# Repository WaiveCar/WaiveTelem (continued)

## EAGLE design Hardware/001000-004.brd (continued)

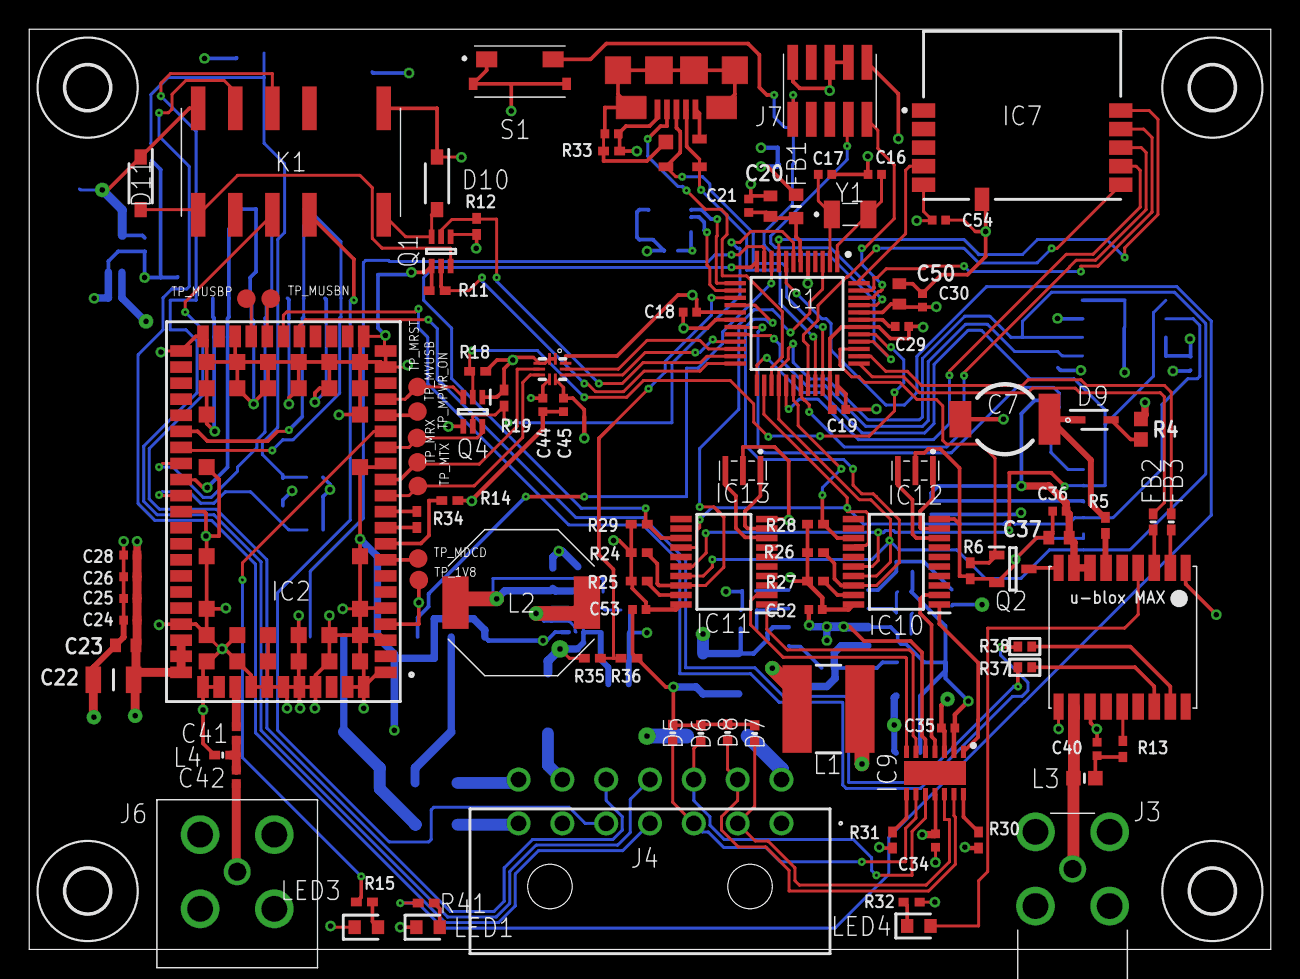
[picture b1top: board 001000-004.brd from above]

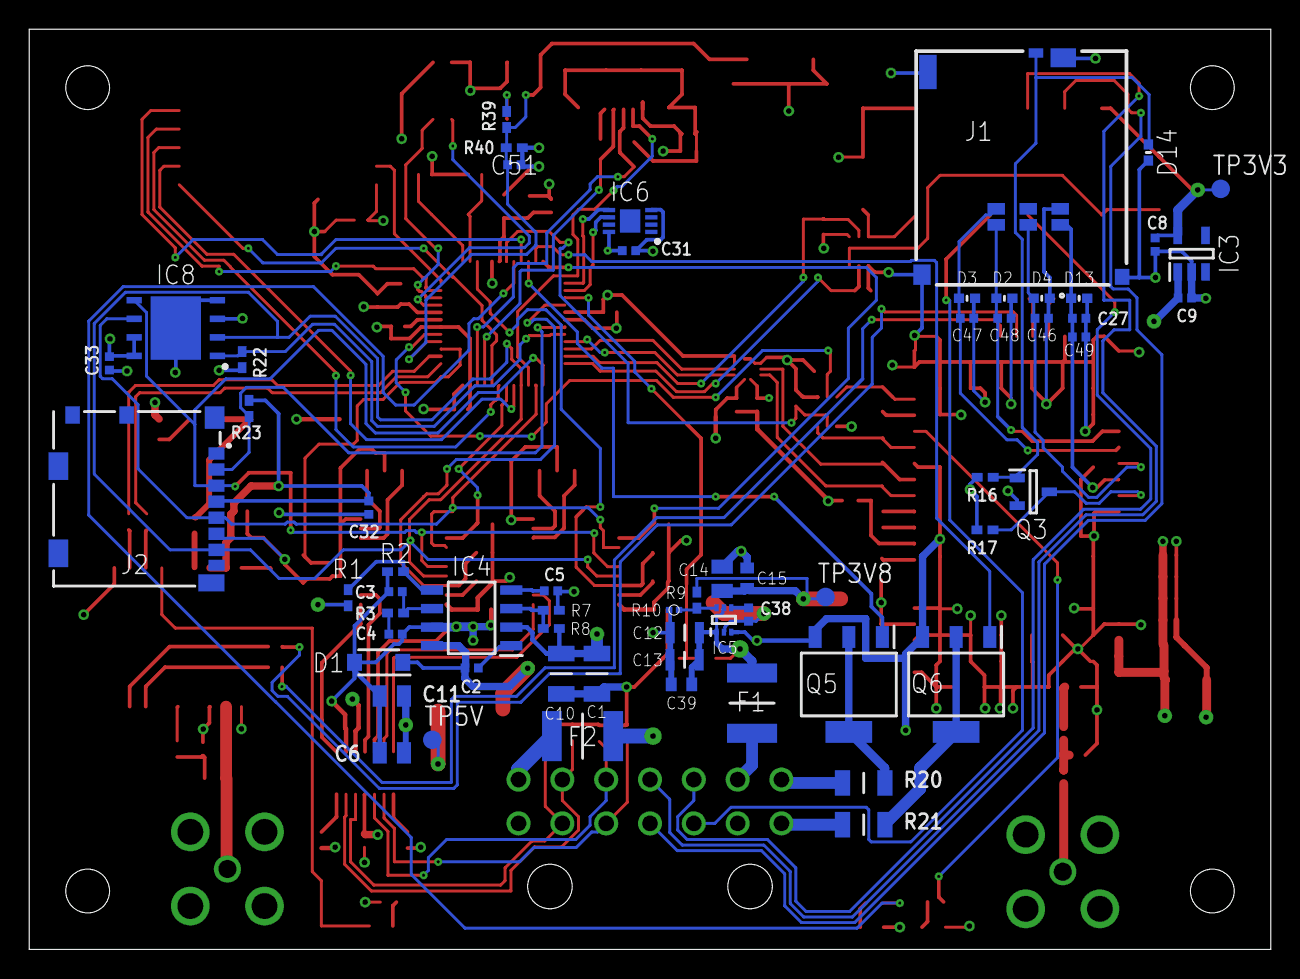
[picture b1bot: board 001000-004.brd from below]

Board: 4 copper layers, 85.0 x 63.0 mm, 168 parts (61 on the bottom side), 125 nets.

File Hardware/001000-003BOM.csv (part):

"Qty";"Value";"Device";"Package";"Parts";"Description";"CODE-ARDUINO";"DATASHEET";"DESCRIPTION";"DISTRIBUTOR-LINK";"DISTRIBUTOR-PN";"HEIGHT";"MANUFACTURER";"MANUFACTURER-PN";"MANUFACTURER_NAME";"MANUFACTURER_PART_NUMBER";"MOUSER_PART_NUMBER";"MOUSER_PRICE-STOCK";"NOTE";"RS_PART_NUMBER";"RS_PRICE-STOCK";"TP_SIGNAL_NAME";"VALUE";
"1";"-";"USB-MICRO";"ZX62-AB-5PA";"J5";"USB - micro AB USB 2.0 Receptacle Connector 5 Position Surface Mount, Right Angle, Horizontal";"2219";"https://www.hirose.com/product/en/download_file/key_name/ZX/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";"";"http://www.digikey.com/product-detail/en/hirose-electric-co-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";"H125279CT-ND ";"";"Hirose";"ZX62-AB-5PA(31) ";"";"";"";"";"";"";"";"";"-";
"3";"0R";"R_0402";"R0402";"R5, R14, R34";"RESISTOR";"";"";"";"";"";"";"";"";"";"";"";"";"";"";"";"";"";
"2";"0R";"R_1206";"R1206";"R20, R21";"RESISTOR";"";"";"";"";"";"";"";"";"";"";"";"";"";"";"";"";"";
"17";"100n";"C_0402";"C0402";"C2, C18, C19, C21, C24, C27, C30, C31, C33, C34, C35, C38, C44, C45, C52, C53, C54";"NON-POLARIZED CAP";"";"";"";"";"";"";"";"";"";"";"";"";"";"";"";"";"";
"1";"100p";"C-4N7-0402";"0402-1005X55N";"C51";"SMD Capacitor";"2266";"http://search.murata.co.jp/Ceramy/image/img/A01X/partnumberi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";"";"https://www.digikey.com/product-detail/en/murata-electronics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";"490-8259-1-ND";"";"Murata";"GRM155R71H472KA01J";"";"";"";"";"-";"";"";"";"4n7";
"1";"100u";"C_1206";"C1206";"C22";"NON-POLARIZED CAP";"";"";"";"";"";"";"";"";"";"";"";"";"";"";"";"";"";
"1";"1040310811";"1040310811";"1040310811";"J2";"MICRO SD card socket, push-pull 1.42H Normal type";"";"";"MICRO SD card socket, push-pull 1.42H Normal type";"";"";"mm";"";"";"Molex";"1040310811";"N/A";"https://www.mouser.com/Search/Refine.aspx?Keyword=N%2FA";"";"";"";"";"";
"1";"10R";"R_0402";"R0402";"R13";"RESISTOR";"";"";"";"";"";"";"";"";"";"";"";"";"";"";"";"";"";
"5";"10k";"R_0402";"R0402";"R15, R22, R23, R36, R40";"RESISTOR";"";"";"";"";"";"";"";"";"";"";"";"";"";"";"";"";"";
"1";"10k";"R_0603";"R0603";"R4";"RESISTOR";"";"";"";"";"";"";"";"";"";"";"";"";"";"";"";"";"";
"1";"10k2";"CRCW040210K2FKED";"RESC1005X40N";"R1";"CRCW0402 Resistor T/R 0.063W,1%,10K2 Vishay CRCW Series Thick Film Surface Mount Resistor 0402 Case 10.2k +/-1% 0.063W +/-100ppm/C";"";"";"CRCW0402 Resistor T/R 0.063W,1%,10K2 Vishay CRCW Series Thick Film Surface Mount Resistor 0402 Case 10.2k +/-1% 0.063W +/-100ppm/C";"";"";"0.4mm";"";"";"Vishay";"CRCW040210K2FKED";"71-CRCW0402-10.2K-E3";"https://www.mouser.com/Search/Refine.aspx?Keyword=71-CRCW040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";"";"";"";"";"";
"8";"10k2";"R_0402";"R0402";"R24, R25, R26, R27, R28, R29, R30, R31";"RESISTOR";"";"";"";"";"";"";"";"";"";"";"";"";"";"";"";"";"";
"1";"10n";"C_0402";"C0402";"C25";"NON-POLARIZED CAP";"";"";"";"";"";"";"";"";"";"";"";"";"";"";"";"";"";
"1";"10nF";"C_0402";"C0402";"C40";"NON-POLARIZED CAP";"";"";"";"";"";"";"";"";"";"";"";"";"";"";"";"";"";
"1";"10p";"C_0402";"C0402";"C3";"NON-POLARIZED CAP";"";"";"";"";"";"";"";"";"";"";"";"";"";"";"";"";"";
"1";"10u";"C_0402";"C0402";"C32";"NON-POLARIZED CAP";"";"";"";"";"";"";"";"";"";"";"";"";"";"";"";"";"";
"3";"10u";"C_0603";"C0603";"C20, C23, C50";"NON-POLARIZED CAP";"";"";"";"";"";"";"";"";"";"";"";"";"";"";"";"";"";
"2";"10u";"C_0805";"C0805";"C6, C11";"NON-POLARIZED CAP";"";"";"";"";"";"";"";"";"";"";"";"";"";"";"";"";"";
"1";"15p";"C_0402";"C0402";"C28";"NON-POLARIZED CAP";"";"";"";"";"";"";"";"";"";"";"";"";"";"";"";"";"";
"8";"1M2";"R_0402";"R0402";"R6, R11, R12, R16, R17, R18, R19, R33";"RESISTOR";"";"";"";"";"";"";"";"";"";"";"";"";"";"";"";"";"";
"1";"1k96";"CRCW04021K96FKED";"RESC1005X40N";"R2";"Vishay CRCW Series Thick Film Surface Mount Resistor 0402 Case 1.96k +/-1% 0.063W +/-100ppm/C";"";"";"Vishay CRCW Series Thick Film Surface Mount Resistor 0402 Case 1.96k +/-1% 0.063W +/-100ppm/C";"";"";"0.4mm";"";"";"Vishay";"CRCW04021K96FKED";"71-CRCW0402-1.96K-E3";"https://www.mouser.com/Search/Refine.aspx?Keyword=71-CRCW040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";"";"";"";"";"";
"3";"1u";"C_0402";"C0402";"C8, C9, C29";"NON-POLARIZED CAP";"";"";"";"";"";"";"";"";"";"";"";"";"";"";"";"";"";
"1";"1u";"C_0603";"C0603";"C37";"NON-POLARIZED CAP";"";"";"";"";"";"";"";"";"";"";"";"";"";"";"";"";"";
"2";"20p";"C_0402";"C0402";"C16, C17";"NON-POLARIZED CAP";"";"";"";"";"";"";"";"";"";"";"";"";"";"";"";"";"";
"1";"27nH";"L-14C27NJV4T";"INDC1608X95N";"L3";"Inductor RF Chip Multi-Layer 27nH 5% 100MHz 10Q-Factor Ceramic 300mA 600mOhm DCR 0603 T/R";"";"";"Inductor RF Chip Multi-Layer 27nH 5% 100MHz 10Q-Factor Ceramic 300mA 600mOhm DCR 0603 T/R";"";"";"0.95mm";"";"";"JOHANSON TECHNOLOGY";"L-14C27NJV4T";"";"";"";"";"";"";"";
"1";"28k";"R_0402";"R0402";"R3";"RESISTOR";"";"";"";"";"";"";"";"";"";"";"";"";"";"";"";"";"";
"2";"2N7002,215";"2N7002,215";"SOT95P230X110-3N";"Q2, Q3";"MOSFET N-Channel 60V 0.3A TO236AB NXP 2N7002,215 N-channel MOSFET Transistor, 0.3 A, 60 V, 3-Pin TO-236AB";"";"";"MOSFET N-Channel 60V 0.3A TO236AB NXP 2N7002,215 N-channel MOSFET Transistor, 0.3 A, 60 V, 3-Pin TO-236AB";"";"";"1.1mm";"";"";"Nexperia";"2N7002,215";"771-2N7002-T/R";"https://www.mouser.com/Search/Refine.aspx?Keyword=771-2N7002-T%2FR";"";"";"";"";"";
"2";"2N7002DW-7-F";"2N7002DW-7-F";"SOT65P210X100-6N";"Q1, Q4";"Diodes Inc 2N7002DW-7-F Dual N-channel MOSFET, 115 mA, 60 V, 6-Pin SOT-363";"";"";"Diodes Inc 2N7002DW-7-F Dual N-channel MOSFET, 115 mA, 60 V, 6-Pin SOT-363";"";"";"1mm";"";"";"Diodes Inc.";"2N7002DW-7-F";"621-2N7002DW-F";"https://www.mouser.com/Search/Refine.aspx?Keyword=621-2N7002DW-F";"";"";"";"";"";
"1";"2n2";"C_0402";"C0402";"C4";"NON-POLARIZED CAP";"";"";"";"";"";"";"";"";"";"";"";"";"";"";"";"";"";
"1";"39R";"R_0402";"R0402";"R39";"RESISTOR";"";"";"";"";"";"";"";"";"";"";"";"";"";"";"";"";"";
"1";"40k";"R_0402";"R0402";"R35";"RESISTOR";"";"";"";"";"";"";"";"";"";"";"";"";"";"";"";"";"";
"1";"43045-1400";"43045-1400";"43045-1400";"J4";"14 way microfit 3mm dual row r/a header Molex MICRO-FIT 3.0 Series, Series Number 43045, 3mm Pitch 14 Way 2 Row Shrouded Right Angle PCB Header, Through Hole";"";"";"14 way microfit 3mm dual row r/a header Molex MICRO-FIT 3.0 Series, Series Number 43045, 3mm Pitch 14 Way 2 Row Shrouded Right Angle PCB Header, Through Hole";"";"";"mm";"";"";"Molex";"43045-1400";"538-43045-1400";"https://www.mouser.com/Search/Refine.aspx?Keyword=538-43045-1400";"";"";"";"";"";
"1";"470R";"R_0402";"R0402";"R32";"RESISTOR";"";"";"";"";"";"";"";"";"";"";"";"";"";"";"";"";"";
"1";"47p";"C_0402";"C0402";"C36";"NON-POLARIZED CAP";"";"";"";"";"";"";"";"";"";"";"";"";"";"";"";"";"";
"1";"4n7";"C-4N7-0402";"0402-1005X55N";"C43";"SMD Capacitor";"2266";"http://search.murata.co.jp/Ceramy/image/img/A01X/partnumberi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";"";"https://www.digikey.com/product-detail/en/murata-electronics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";"490-8259-1-ND";"";"Murata";"GRM155R71H472KA01J";"";"";"";"";"-";"";"";"";"4n7";
"1";"68p";"C_0402";"C0402";"C26";"NON-POLARIZED CAP";"";"";"";"";"";"";"";"";"";"";"";"";"";"";"";"";"";
"1";"8n2";"C_0402";"C0402";"C5";"NON-POLARIZED CAP";"";"";"";"";"";"";"";"";"";"";"";"";"";"";"";"";"";
"1";"ABS07-32.768KHZ-1-T";"ABS07-32.768KHZ-1-T";"ABS0716632768KHZT";"Y1";"Abracon 32.768kHz Crystal Unit +/-10ppm SMD 2-Pin 3.2 x 1.5 x 0.9mm";"";"";"Abracon 32.768kHz Crystal Unit +/-10ppm SMD 2-Pin 3.2 x 1.5 x 0.9mm";"";"";"0.9mm";"";"";"ABRACON";"ABS07-32.768KHz-1-T";"815-ABS07-32.7K-1-T";"https://www.mouser.com/Search/Refine.aspx?Keyword=815-ABS07-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";"";"";"";"";"";
"1";"AP2112K-3.3TRG1";"AP2112K-3.3TRG1";"SOT95P282X130-5N";"IC3";"600mA 3.3V LDO Regulator Enable SOT23-5 DiodesZetex AP2112K-3.3TRG1, LDO Voltage Regulator, 3.3 V +/-1.5%, 2.5  6 Vin, 5-Pin SOT-23";"";"";"600mA 3.3V LDO Regulator Enable SOT23-5 DiodesZetex AP2112K-3.3TRG1, LDO Voltage Regulator, 3.3 V +/-1.5%, 2.5  6 Vin, 5-Pin SOT-23";"";"";"1.3mm";"";"";"Diodes Inc.";"AP2112K-3.3TRG1";"621-AP2112K-3.3TRG1";"https://www.mouser.com/Search/Refine.aspx?Keyword=621-AP2112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";"";"";"";"";"";
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
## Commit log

2019-06-26 adding hardware files including schematic and board layout
2019-06-26 adding the arduino-based firmware
2019-06-28 adding arduino libaries and pcb -004. the 004 board adds a 2A incoming resettable fuse as well as renames the nets from the uC to understandable names
2019-07-01 adding pick and place files
2019-07-02 initial checking plug-provision
2019-07-03 plug-firmware initial checkin
2019-07-03 add MQTT
2019-07-03 fix mkrnb1500 compilation error
2019-07-03 add handling commands
2019-07-04 check in README.md
2019-07-04 add STBLE library
2019-07-05 update README.me for windows installation
2019-07-05 add SD as lib_deps
2019-07-05 update scripts to make them work on Windows
2019-07-05 update run.sh for different OSs
2019-07-05 verify provisioning works on Windows
2019-07-07 implement GPS
2019-07-08 add CAN configuration
2019-07-08 add can.canbus configuration
2019-07-09 reduce memory usage
2019-07-10 use different JSON parser
2019-07-10 add firmware status reporting
2019-07-11 go back to ArduinoJson
2019-07-11 checkin ArduinoBearSSL as library
2019-07-11 update ArduinoBearSSL to reduce memory usage
2019-07-11 make WIFI_SSID and WIFI_PASSWORD env variable
2019-07-11 update to platformio 4.0.0 and add httpClient
2019-07-12 add SD firmware update
2019-07-12 refactor SystemClass
2019-07-14 add http
2019-07-14 S3 bucket firmware upgrade
2019-07-14 fix firmware OTA update
2019-07-16 update config
2019-07-16 implement sendCanStatus
2019-07-16 add modified NeoGPS in lib
2019-07-16 System.cpp clean up
2019-07-17 add copy, reboot commands
2019-07-17 update flashFirmware.sh for windows
2019-07-17 clean up provision scripts
2019-07-17 change Console to Logger
2019-07-17 add logError
2019-07-18 change doors to centralLock in json
2019-07-18 check-in appble afte react-native init
2019-07-18 initial appble check-in
2019-07-18 change plug-1 to waive-1
2019-07-19 get app to send
2019-07-20 trying to sleep, still need to fix GPS
2019-07-21 get GPS working well
2019-07-22 move SDU.cpp
2019-07-22 add ios app to beta
2019-07-23 check-in test_crypto reference
2019-07-23 check-in 1.0.5
2019-07-23 fix heartbeat sent twice initial
2019-07-23 schematic pdf
2019-07-23 list of all pin definitions, a specific breakdown for uC and a list of differences between mkr proto and boards
2019-07-24 check-in initial board and variant (copy mkrnb1500)
2019-07-24 change name
2019-07-25 check-in initial waive1000
2019-07-25 enable debugger
2019-07-27 fix GPS
2019-07-27 move telemetry() to System
2019-07-27 rename http to https
2019-07-31 get canbus working
2019-07-31 added code pin numbers
2019-08-01 update provisioning code
2019-08-01 chagne bsp directory
2019-08-02 get base64 decryption working
2019-08-02 get Bluetooth to support message > 20 bytes
2019-08-05 ready for cellular test
2019-08-07 rename appble to plug-appble
2019-08-07 get bluetooth token working
2019-08-08 add bluetooth auth endpoint on lambda
2019-08-09 get MKR GPS working again
2019-08-09 add SDUBoot
2019-08-09 update UPDATE.BIN name
2019-08-10 move GPS.poll() from main to System.poll()
2019-08-12 get Gps.sleep to work
2019-08-14 checking current bluetooth implementation
2019-08-14 use RTCZero to sleep
2019-08-15 get bluetooth security working
2019-08-15 optimize power saving
2019-08-15 release app 1.0.4
2019-08-16 get android app working
2019-08-16 separate command and system
2019-08-16 log json
2019-08-17 refactor
2019-08-17 check in ArduinoMqttClient as lib before modifying
2019-08-17 make mqtt message size max 512
2019-08-18 make logging level configurable
2019-08-19 improve json logging
2019-08-19 failure checkings
2019-08-20 make begin() return status
2019-08-20 add JsonBuilder
2019-08-21 add RTCZero to lib
2019-08-21 update RTCZero to sleep without reset
2019-08-21 no real change
2019-08-23 who cares it's just a text file
2019-08-23 Update whocares.txt
    i added stuff
2019-08-23 Update whocares.txt
    more changes
2019-08-23 more updates
2019-08-23 Top and Bottom
2019-08-23 change DOOR_UNLOCK_PIN to active low
2019-08-23 Files sent to DFM guys
2019-08-23 read VIN_SENSE
2019-08-24 update canbus
2019-08-25 add can cmd
2019-08-26 add can bus cmd to mobile app
2019-08-28 use unchanged ArduinoBearlSSL
2019-08-28 adjust mqtt watchdog settings
2019-08-28 print MODEM firmware version
2019-08-29 update for Windows
2019-08-29 case_bottom2 and case_top2_logo are 3D printed
2019-08-29 provision 3 more waive1000
2019-08-30 fix CAN BUS #2
2019-08-30 uncomment Mqtt.poll()
2019-08-30 comment out write to file for now
2019-08-30 separate can bus 0 and can bus 1 initialization
2019-08-31 fix can mask
2019-08-31 fix rm -rf ~/.platformio/packages/framework-arduinosam/variants/waive1000
2019-08-31 update JsonLogger to escape chars
2019-08-31 remove JsonLogger
2019-08-31 get rid of STBLE __pack warning
2019-09-03 fix canbus commands
2019-09-04 fix mqtt cmd
2019-09-04 add some debug statements
2019-09-04 reduce CANBUS buffer size
2019-09-04 adding debug code to troubleshoot multiple certs
2019-09-04 clarify how to update CONFIG.TXT
2019-09-04 fix inRide not working
2019-09-05 put vin in heartbeat
2019-09-05 fix MQTT connection issue
2019-09-05 use WDTZero for watchdog
2019-09-06 updated filename convention
2019-09-06 save MQTT config on EEPROM
2019-09-07 cleanup code
2019-09-09 add crash report
2019-09-10 these two have hologram so updated config
2019-09-10 make sure can bus data less than delta will be tx
2019-09-10 checking unchanged ECCX08 first
2019-09-10 update checkCrashReport to check len > 0
2019-09-10 use delayMicroseconds in ECCX08 to work in ISR
2019-09-11 add set remote log level
2019-09-12 batch can bus telemetry
2019-09-12 add timestamp to the crash report
2019-09-12 add debug flag in sysInfo
2019-09-12 fix reboot()
2019-09-12 use len for log sender
2019-09-13 switch to a smaller Base64 lib
2019-09-13 use ignition to determin heartbeat interval
2019-09-13 1.1.7
2019-09-13 save immo State to IMMO.TXT
2019-09-14 update mobile app and https download
2019-09-16 setTime in getDateTime()
2019-09-16 change MKRNB to allow overriding default root cert
2019-09-16 move some lib to github
2019-09-17 grab JsonLogger from github instead
2019-09-17 add better motion detection
2019-09-17 import WDTZero from github
2019-09-17 clean up BLE SPI3 to be SPI1
2019-09-17 check in .pio/libdeps so not relying on cloud
2019-09-18 move BLESPI definition back to arduino_bluenrg_ble
2019-09-18 change inRide to ignitionOn in CONFIG.TXT
2019-09-18 fix can bus batch report
2019-09-19 get https config download working
2019-09-19 update provision firmware to disable OTA update
2019-09-19 use Arduino version of SD
2019-09-19 get time from gps if internnet not available
2019-09-20 1.1.10
2019-09-21 1.2.1 fixing mqtt cmd delay issue
2019-09-22 1.2.2 MCU low-power mode turned on for release
2019-09-26 1.2.3 remove Mqtt.poll from setup()
2019-09-26 update default firmware
2019-09-27 add simIgnition
2019-10-02 app update
2019-10-02 use hashmaps for can bus status to avoid memory leak
2019-10-03 handle System.sleep() interruption
2019-10-04 improve motion detection
2019-10-07 add disableModemFirmwareUpdate in Cellular.cpp
2019-10-10 not to retry if can bus returns error
2019-10-11 fix canbus ignition detection
2019-10-15 attempt to fix mqtt delay issue
2019-10-15 add InternetClass::begin()
2019-10-15 workaround File.seek issue
2019-10-17 improve Modem check
2019-10-17 005 hardware revision
2019-10-23 update bluetooth
2019-10-23 fix invalid heartbeat json
2019-10-24 update release
2019-10-25 1.3.2 disable sleeping; clean up
2019-10-28 change lock_rear to lock_back to be consistent
2019-10-28 fix door_back_left and right
2019-10-29 1.3.3: allow indefinite cellular registration
2019-12-18 fixed the condition where we lost AT in the middle of operation, issue 73
2019-12-19 -005 board updates
2020-02-06 DFM ready (draft) without some updates
2020-02-06 DFM ready case bottom
2020-02-06 Top and bottom, no DFM, small USB port, wider coax
2020-02-20 Latest revision
2020-02-20 this includes instructions on how to produce cases
